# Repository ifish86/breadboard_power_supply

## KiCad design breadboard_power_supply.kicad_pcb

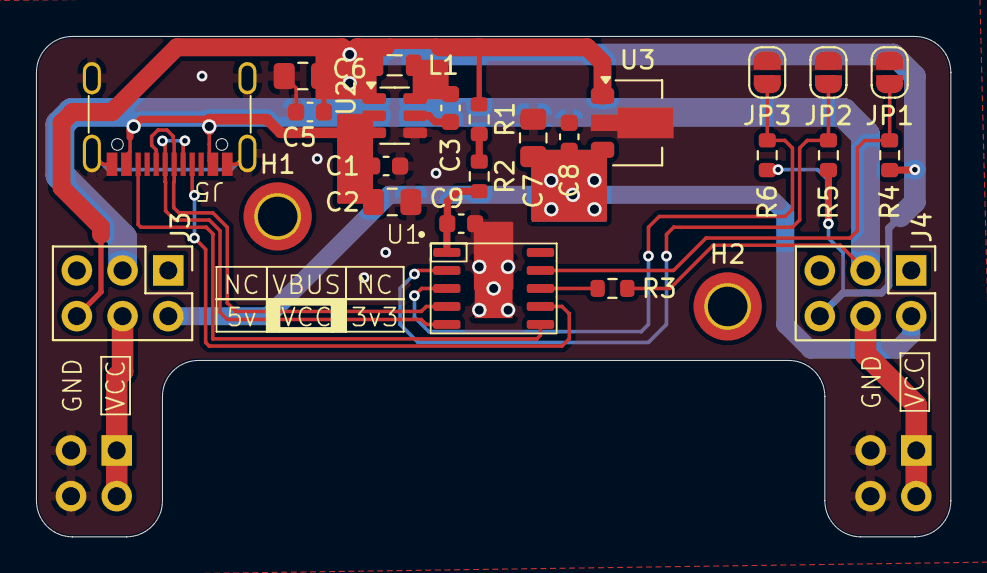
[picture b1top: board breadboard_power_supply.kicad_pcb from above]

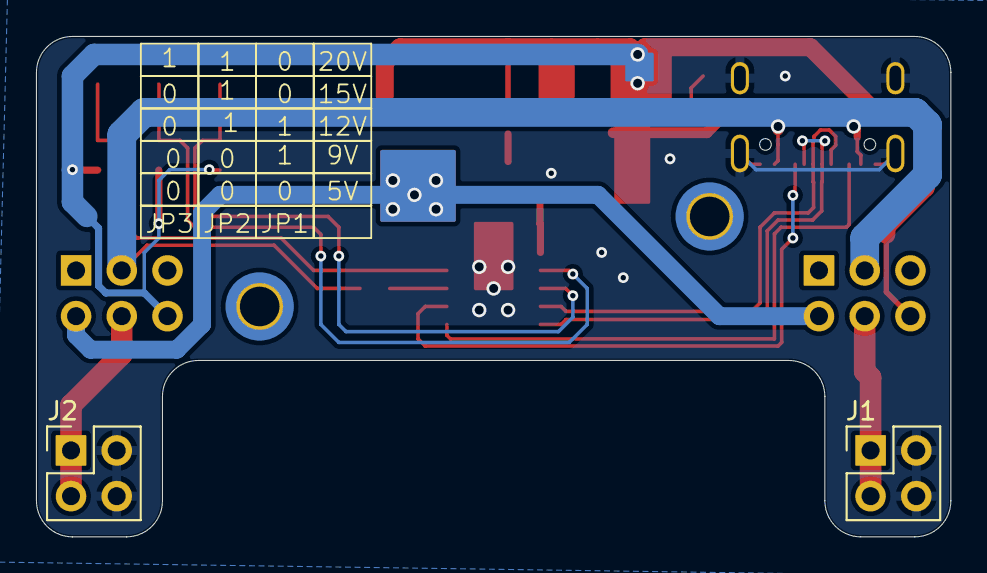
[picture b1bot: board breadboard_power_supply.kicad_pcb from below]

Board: 2 copper layers, 50.8 x 27.8 mm, 28 parts (2 on the bottom side), 18 nets.

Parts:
C1, C3, C5, C8, C9: 100n; C_0603_1608Metric
C2, C6, C7: 10u; C_0805_2012Metric_Pad1.18x1.45mm_HandSolder
H1, H2: MountingHole; MountingHole_2.2mm_M2_DIN965_Pad_TopBottom
J1, J2: Conn_02x02_Odd_Even; PinHeader_2x02_P2.54mm_Vertical
J3, J4: Conn_02x03_Odd_Even; PinHeader_2x03_P2.54mm_Vertical
J5: 7010ASV; GT-USB-7010ASV
JP1, JP2, JP3: SolderJumper_2_Open; SolderJumper-2_P1.3mm_Open_RoundedPad1.0x1.5mm
L1: 4.7uH/800mA; L_0805_2012Metric
R1, R2: 100; R_0603_1608Metric_100
R3, R4: 10k; R_0603_1608Metric_10k
R5, R6: 1k; R_0603_1608Metric_1k
U1: CH224K
U2: AP63205; SOT-23-6
U3: AP2205-33Y; SOT-89-3

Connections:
+3.3V: C7.1, C8.1, J3.2, J4.2, U3.3 (VO)
+5V: C5.1, C6.1, J3.6, J4.6, L1.2, R1.1, R4.2, R5.2, R6.2, U2.1 (FB), U3.1 (VI)
/CC1: J5.A5 (CC1), U1.7 (CC1)
/CC2: J5.B5 (CC2), U1.6 (CC2)
/CFG1: JP1.2 (B), R4.1, U1.9 (CFG1)
/CFG2: JP2.2 (B), R5.1, U1.2 (CFG2)
/CFG3: JP3.2 (B), R6.1, U1.3 (CFG3)
/USB_N: J5.A7 (D-), J5.B7 (D-), U1.5 (DM)
/USB_P: J5.A6 (D+), J5.B6 (D+), U1.4 (DP)
GND: C1.2, C2.2, C5.2, C6.2, C7.2, C8.2, C9.2, J1.2, J1.4, J2.2, J2.4, J5.A1_B12 (GND), J5.B1_A12 (GND), J5.S1 (SHIELD), JP1.1 (A), JP2.1 (A), JP3.1 (A), U1.11 (GND), U2.4 (GND), U3.2 (GND)
unnamed: R1.2, R2.1
unnamed: R3.1, U1.8 (VBUS)
unnamed: C9.1, R2.2, U1.1 (Vdd)
unnamed: C3.2, L1.1, U2.6 (BST)
unnamed: C3.1, U2.5 (SW)
VBUS: C1.1, C2.1, J3.3, J4.3, J5.A4_B9 (VBUS), J5.B4_A9 (VBUS), R3.2, U2.2 (EN), U2.3 (IN)
VCC_O1: J1.1, J1.3, J3.4
VCC_O2: J2.1, J2.3, J4.4

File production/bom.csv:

Designator,Footprint,Quantity,Value,LCSC Part #
"C1, C3, C5, C8, C9",0603,5,100n,C14663
"C2, C6, C7",0805,3,10u,C440198
"J1, J2",PinHeader_2x02_P2.54mm_Vertical,2,Conn_02x02_Odd_Even,
"J3, J4",PinHeader_2x03_P2.54mm_Vertical,2,Conn_02x03_Odd_Even,
J5,GT-USB-7010ASV,1,7010ASV,C2988369
L1,0805,1,4.7uH/800mA,C86090
"R1, R2",0603,2,100,C22775
"R3, R4",0603,2,10k,C25804
"R5, R6",0603,2,1k,C21190
U1,CH224K,1,CH224K,C970725
U2,SOT-23-6,1,AP63205,C2071056
U3,SOT-89-3,1,AP2205-33Y,

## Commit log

2025-10-20 started PCB board shape and part placement
2025-10-21 part placement done, started routing of top layer
2025-10-25 adjusted position for breadboard connectors
2025-11-30 added production files
